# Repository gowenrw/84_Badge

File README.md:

# 84_Badge

This is where all the files for 84_Badge will be stored.  
This includes code and art and cad and fab files.  All the things.

View the web based Documentation here https://84badge.com

## File Structure

This is the file structure of this repository

* [/](/README.md) - YOU ARE HERE
* [/art/](./art/) - Artwork and other graphics created by this project
  * ./inspiration/ - Art and graphics pulled from other sources used as inspiration for this project
* [/code/](./code/) - All project related Code / Firmware
  * ./dev/ - Code folder for initial development PCB(s)
  * ./prod/ - Code folder for the production PCB(s)
  * ./include/ - Common code includes (e.g. chipset drivers, etc.) used by the other code folders
* [/docs/](./docs/) - Documentation created by this project including web pages
* [/eda/](./eda/) - Electronic Design Automation files (i.e. KiCad)
  * ./dev/ - KiCad project folder for initial development PCB(s)
  * ./prod/ - KiCad project folder for the production PCB(s)
* [/reference_parts/](./reference_parts/) - Documentation pulled from other sources related to components
* [./README.md](/README.md) - This File
* [./LICENSE](/LICENSE) - Currently set to MIT

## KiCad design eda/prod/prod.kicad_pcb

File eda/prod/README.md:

# Electronic Design Automation / Production PCB(s)

KiCad project folder for the production PCB(s).

## File Structure

This is the file structure of this repository

* [/](/README.md) - Home
* [/eda](/eda/) - Electronic Design Automation files (i.e. KiCad)
  * [/eda/prod/](/eda/prod/) - YOU ARE HERE
    * ./<filename>.pro - project file. Holds parameters that apply to the entire project (e.g. schematic, PCB layout, etc.).
    * ./<filename>.sch - schematic file.
    * ./<filename>.kicad_pcb - the PCB New layout file.
    * ./<filename>.net - netlist in "Pcbnew" format
    * ./<filename>.bak - backup of schematic file.
    * ./<filename>.kicad_pcb-bak - backup of the new PCB layout file.
    * ./<filename>-cache.lib - a local cache copy of all the symbols used in the schematic
    * ./fp-lib-table - Footprint library list
    * ./sym-lib-table - Schematic library list
    * [./3d_models/](/eda/prod/3d_models/) - This directory contains footprint 3d model files
    * [./gerber/](/eda/prod/gerber/) - This directory contains gerber formatted files for manufacturing
    * [./lib_fp/](/eda/prod/lib_fp/) - This directory contains footprint module directories
    * [./lib_sh/](/eda/prod/lib_sh/) - This directory contains schematic library files
    * [./snapshots/](/eda/prod/snapshots/) - This directory contains prints of schematic / cad files and images of preview / final product

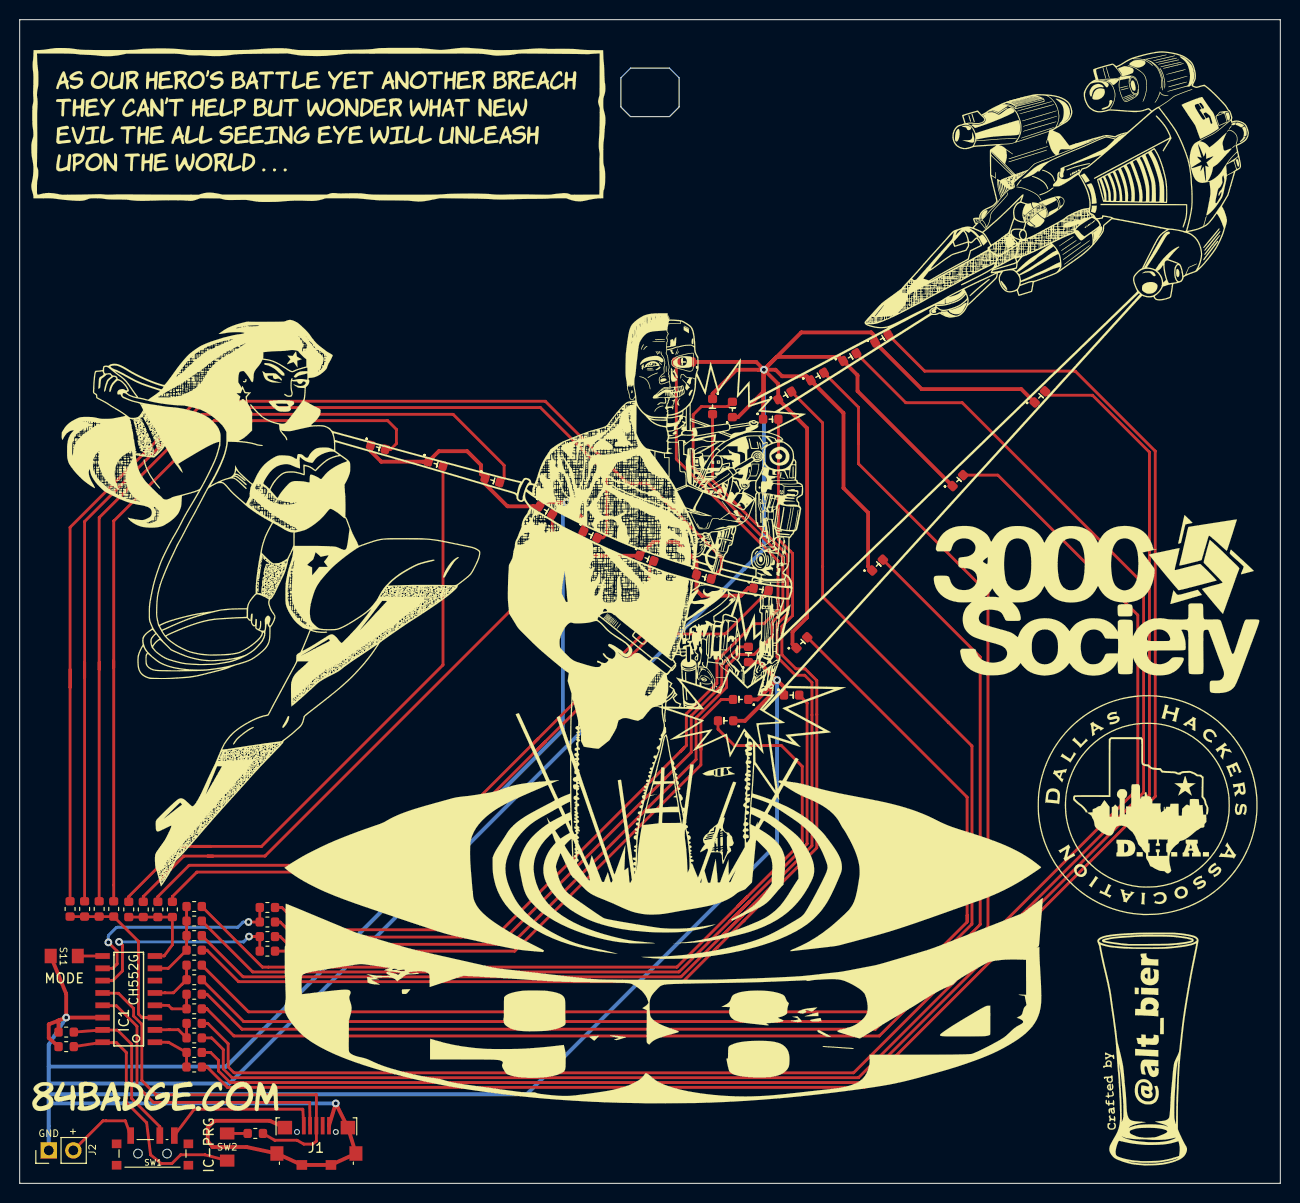
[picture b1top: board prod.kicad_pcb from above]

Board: 2 copper layers, 130.0 x 120.0 mm, 57 parts (0 on the bottom side), 42 nets.

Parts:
C1, C2: 0.1uF/100nF; C_0603_1608Metric
D141, D142, D161, D162, D171, D172, D321, D322: Blue; LED_0603_1608Metric_lowsilk
D151, D152, D153, D154, D301, D302, D303, D304: Yellow; LED_0603_1608Metric_lowsilk
D311, D312, D313, D314, D331, D332, D341, D342: Red; LED_0603_1608Metric_lowsilk
IC1: IC_CH552G; IC_SOIC-16_3.9x9.9mm_Pitch1.27mm
J1: USB_B_Micro; USB_Micro-B_Jing
J2: Conn_01x02; Conn_Pin_Header_Straight_1x02_Pitch2.54mm
R1: 10k Ohms; R_0603_1608Metric
R141, R142, R151, R152, R153, R154, R161, R162, R171, R172, R301, R302, R303, R304, R311, R312, R313, R314, R321, R322, R331, R332, R341, R342: 220 Ohms; R_0603_1608Metric
S11: SW_TS2306A; SW_TS2306A240GFMSM9_C388290
SW1: SPDT_C136659; SW_SPDT_PCM12_C136659
SW2: TS2306A; SW_TS2306A240GFMSM9_C388290

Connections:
BAT-PWR: J2.2, SW1.1
D+: IC1.12, J1.3, R1.1
D-: IC1.13, J1.2
GND: C1.2, C2.2, D141.1, D142.1, D151.1, D152.1, D153.1, D154.1, D161.1, D162.1, D171.1, D172.1, D301.1, D302.1, D303.1, D304.1, D311.1, D312.1, D313.1, D314.1, D321.1, D322.1, D331.1, D332.1, D341.1, D342.1, IC1.14, J1.5, J1.6, J2.1, S11.2
unnamed: D141.2, R141.2
unnamed: D142.2, R142.2
unnamed: D151.2, R151.2
unnamed: D152.2, R152.2
unnamed: D153.2, R153.2
unnamed: D154.2, R154.2
unnamed: D161.2, R161.2
unnamed: D162.2, R162.2
unnamed: D171.2, R171.2
unnamed: D172.2, R172.2
unnamed: D301.2, R301.2
unnamed: D302.2, R302.2
unnamed: D303.2, R303.2
unnamed: D304.2, R304.2
unnamed: D311.2, R311.2
unnamed: D312.2, R312.2
unnamed: D313.2, R313.2
unnamed: D314.2, R314.2
unnamed: D321.2, R321.2
unnamed: D322.2, R322.2
unnamed: D331.2, R331.2
unnamed: D332.2, R332.2
unnamed: D341.2, R341.2
unnamed: D342.2, R342.2
unnamed: R1.2, SW2.2
P1.1: IC1.9, S11.1
P1.4: IC1.2, R141.1, R142.1
P1.5: IC1.3, R151.1, R152.1, R153.1, R154.1
P1.6: IC1.4, R161.1, R162.1
P1.7: IC1.5, R171.1, R172.1
P3.0: IC1.8, R301.1, R302.1, R303.1, R304.1
P3.1: IC1.7, R311.1, R312.1, R313.1, R314.1
P3.2: IC1.1, R321.1, R322.1
P3.3: IC1.10, R331.1, R332.1
P3.4: IC1.11, R341.1, R342.1
USB-PWR: J1.1, SW1.3
V33: C1.1, IC1.16, SW2.1
VCC: C2.1, IC1.15, SW1.2

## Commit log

2020-01-20 Initial Template Upload
2020-01-20 Some Inspiration
2020-01-21 Started Artwork Doodles
2020-01-27 Artwork updates
2020-02-15 badge_silk
2020-03-03 more-silk-work
2020-03-04 silk-screen-art-complete
2020-03-10 Started dev board work
2020-03-11 reference parts updates
2020-03-11 moving reference_parts to its own repository
2020-03-11 adding submodule for reference_parts
2020-03-21 Added 0603 components
2020-03-22 development board finished
2020-04-08 basic code for dev board
2020-05-01 Started work on prod board
2020-05-01 Badge PCB layout work
2020-05-02 More PCB Layout work
2020-05-03 84 badge completed sent to prototype
2020-05-04 First pass at code for the badge
2020-05-13 Updates to LED flashing in Prod code.
2020-05-14 timing in prod code
2020-05-15 documentation work
2020-05-15 updating reference_parts submodule to latest
2020-05-15 more documentation work
2020-05-15 Hero image for web page
2020-05-15 web logo
2020-05-15 web-work
2020-05-16 web site updates
2020-05-16 web site documentation work
2020-05-16 Code documentation.
2020-05-16 typo
2020-05-16 code doc
2020-05-16 syntax highlight error
2020-05-16 code documentation
2020-05-17 EDA documentation
2020-05-17 Create CNAME
2020-05-17 Update to web URL
2020-05-17 web-cleanup
2020-06-14 Adjustments to silkscreen art based on prototype run
2020-07-15 Updates to web docs
2020-07-15 Doc index page update
2020-07-15 Update to index doc page
2022-10-06 Bump addressable from 2.7.0 to 2.8.1 in /docs
    Bumps [addressable](https://github.com/sporkmonger/addressable) from 2.7.0 to 2.8.1.
    - [Release notes](https://github.com/sporkmonger/addressable/releases)
    - [Changelog](https://github.com/sporkmonger/addressable/blob/main/CHANGELOG.md)
    - [Commits](https://github.com/sporkmonger/addressable/compare/addressable-2.7.0...addressable-2.8.1)
    ---
    updated-dependencies:
2022-10-06 Bump nokogiri from 1.10.9 to 1.13.8 in /docs
    Bumps [nokogiri](https://github.com/sparklemotion/nokogiri) from 1.10.9 to 1.13.8.
    - [Release notes](https://github.com/sparklemotion/nokogiri/releases)
    - [Changelog](https://github.com/sparklemotion/nokogiri/blob/main/CHANGELOG.md)
    - [Commits](https://github.com/sparklemotion/nokogiri/compare/v1.10.9...v1.13.8)
    ---
    updated-dependencies:
2022-10-06 Bump tzinfo from 1.2.7 to 1.2.10 in /docs
    Bumps [tzinfo](https://github.com/tzinfo/tzinfo) from 1.2.7 to 1.2.10.
    - [Release notes](https://github.com/tzinfo/tzinfo/releases)
    - [Changelog](https://github.com/tzinfo/tzinfo/blob/master/CHANGES.md)
    - [Commits](https://github.com/tzinfo/tzinfo/compare/v1.2.7...v1.2.10)
    ---
    updated-dependencies:
2022-10-06 Bump activesupport from 6.0.3 to 6.0.6 in /docs
    Bumps [activesupport](https://github.com/rails/rails) from 6.0.3 to 6.0.6.
    - [Release notes](https://github.com/rails/rails/releases)
    - [Changelog](https://github.com/rails/rails/blob/v7.0.4/activesupport/CHANGELOG.md)
    - [Commits](https://github.com/rails/rails/compare/v6.0.3...v6.0.6)
    ---
    updated-dependencies:
2022-10-06 doc theme update
